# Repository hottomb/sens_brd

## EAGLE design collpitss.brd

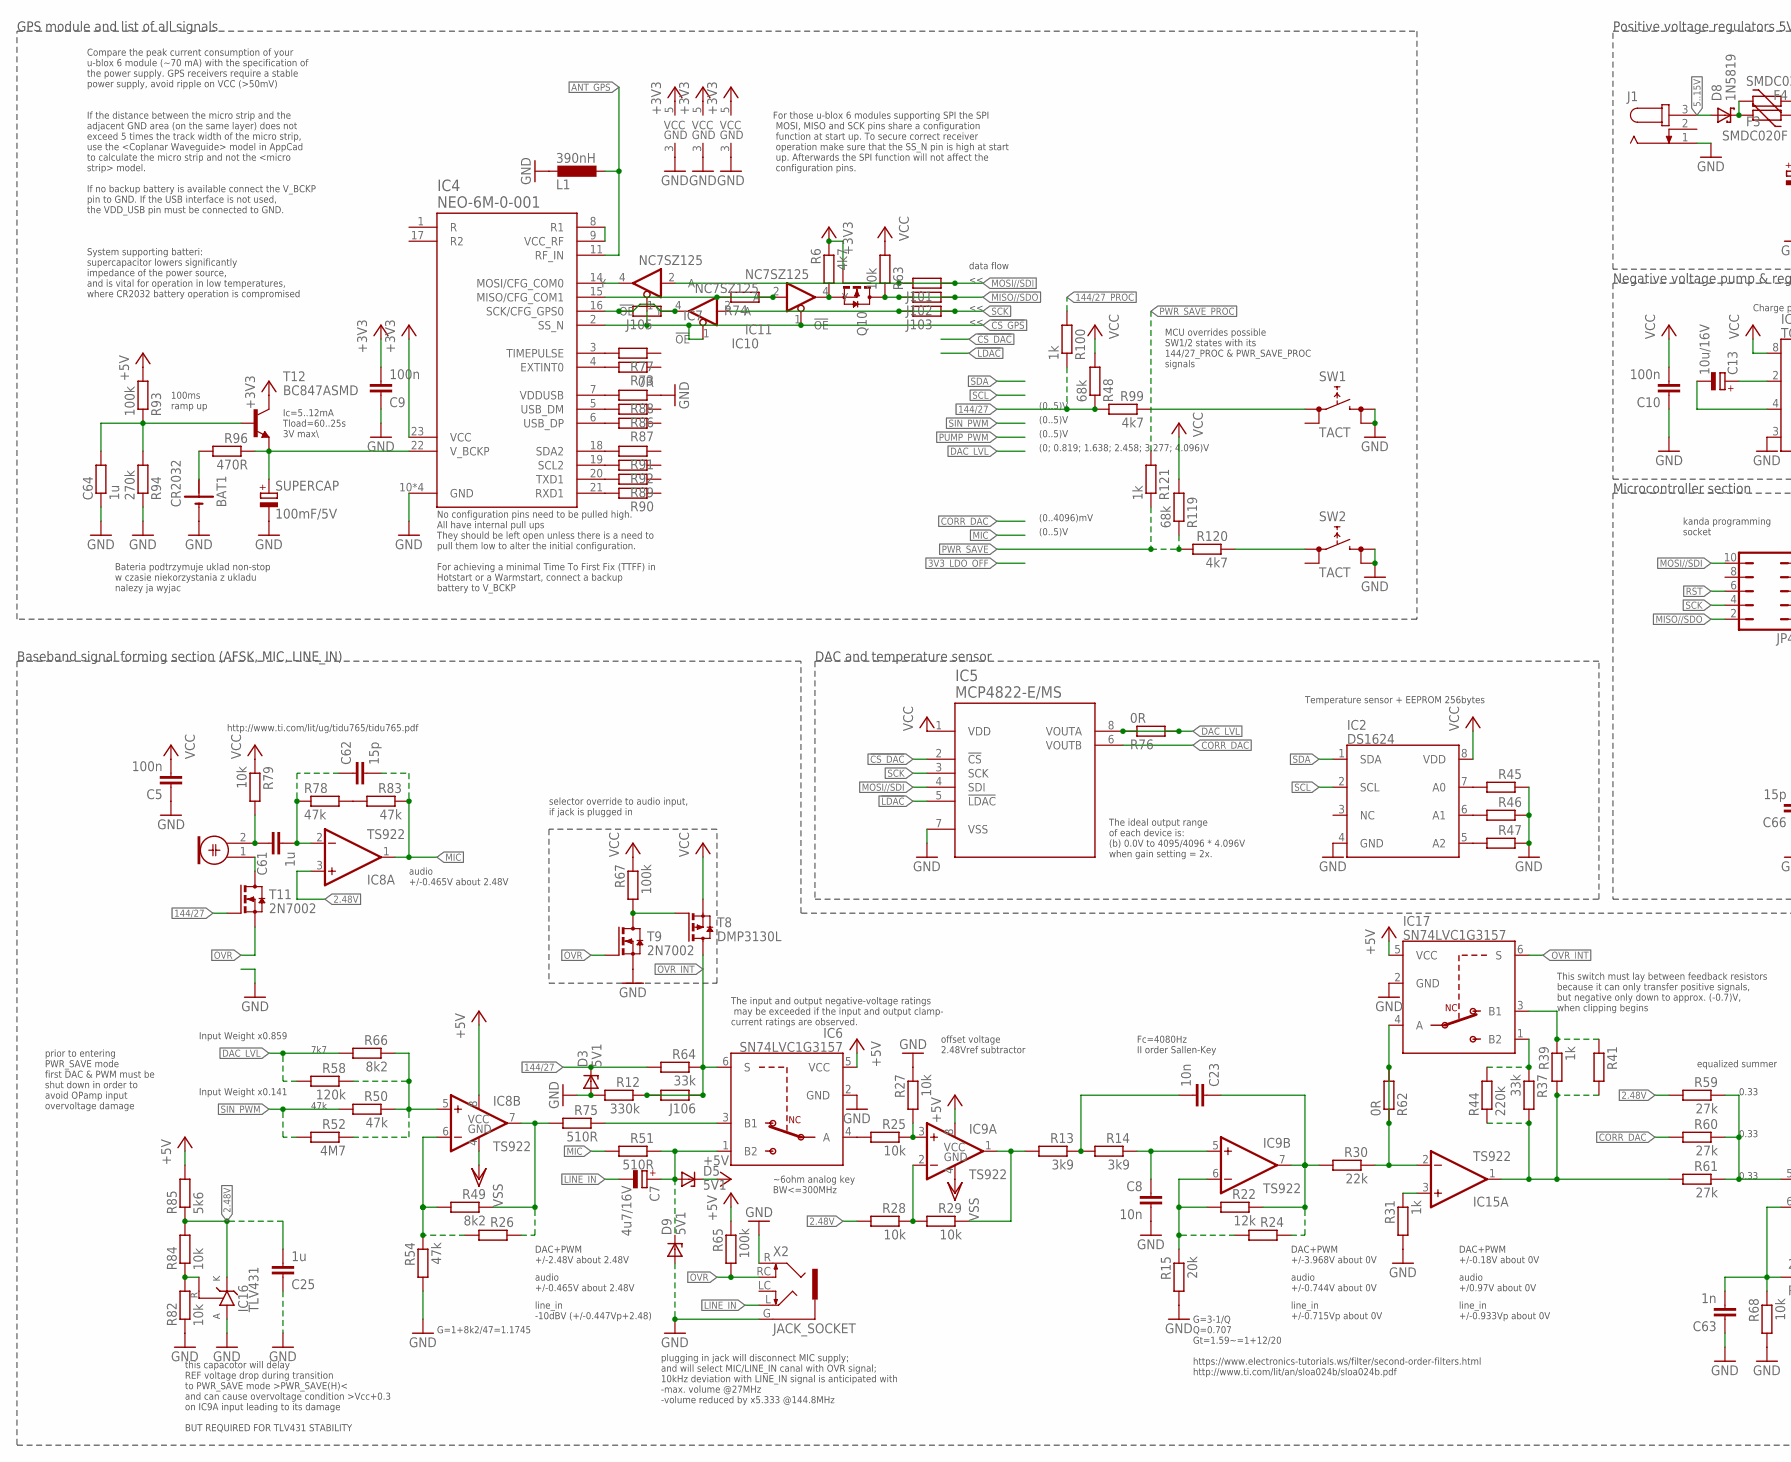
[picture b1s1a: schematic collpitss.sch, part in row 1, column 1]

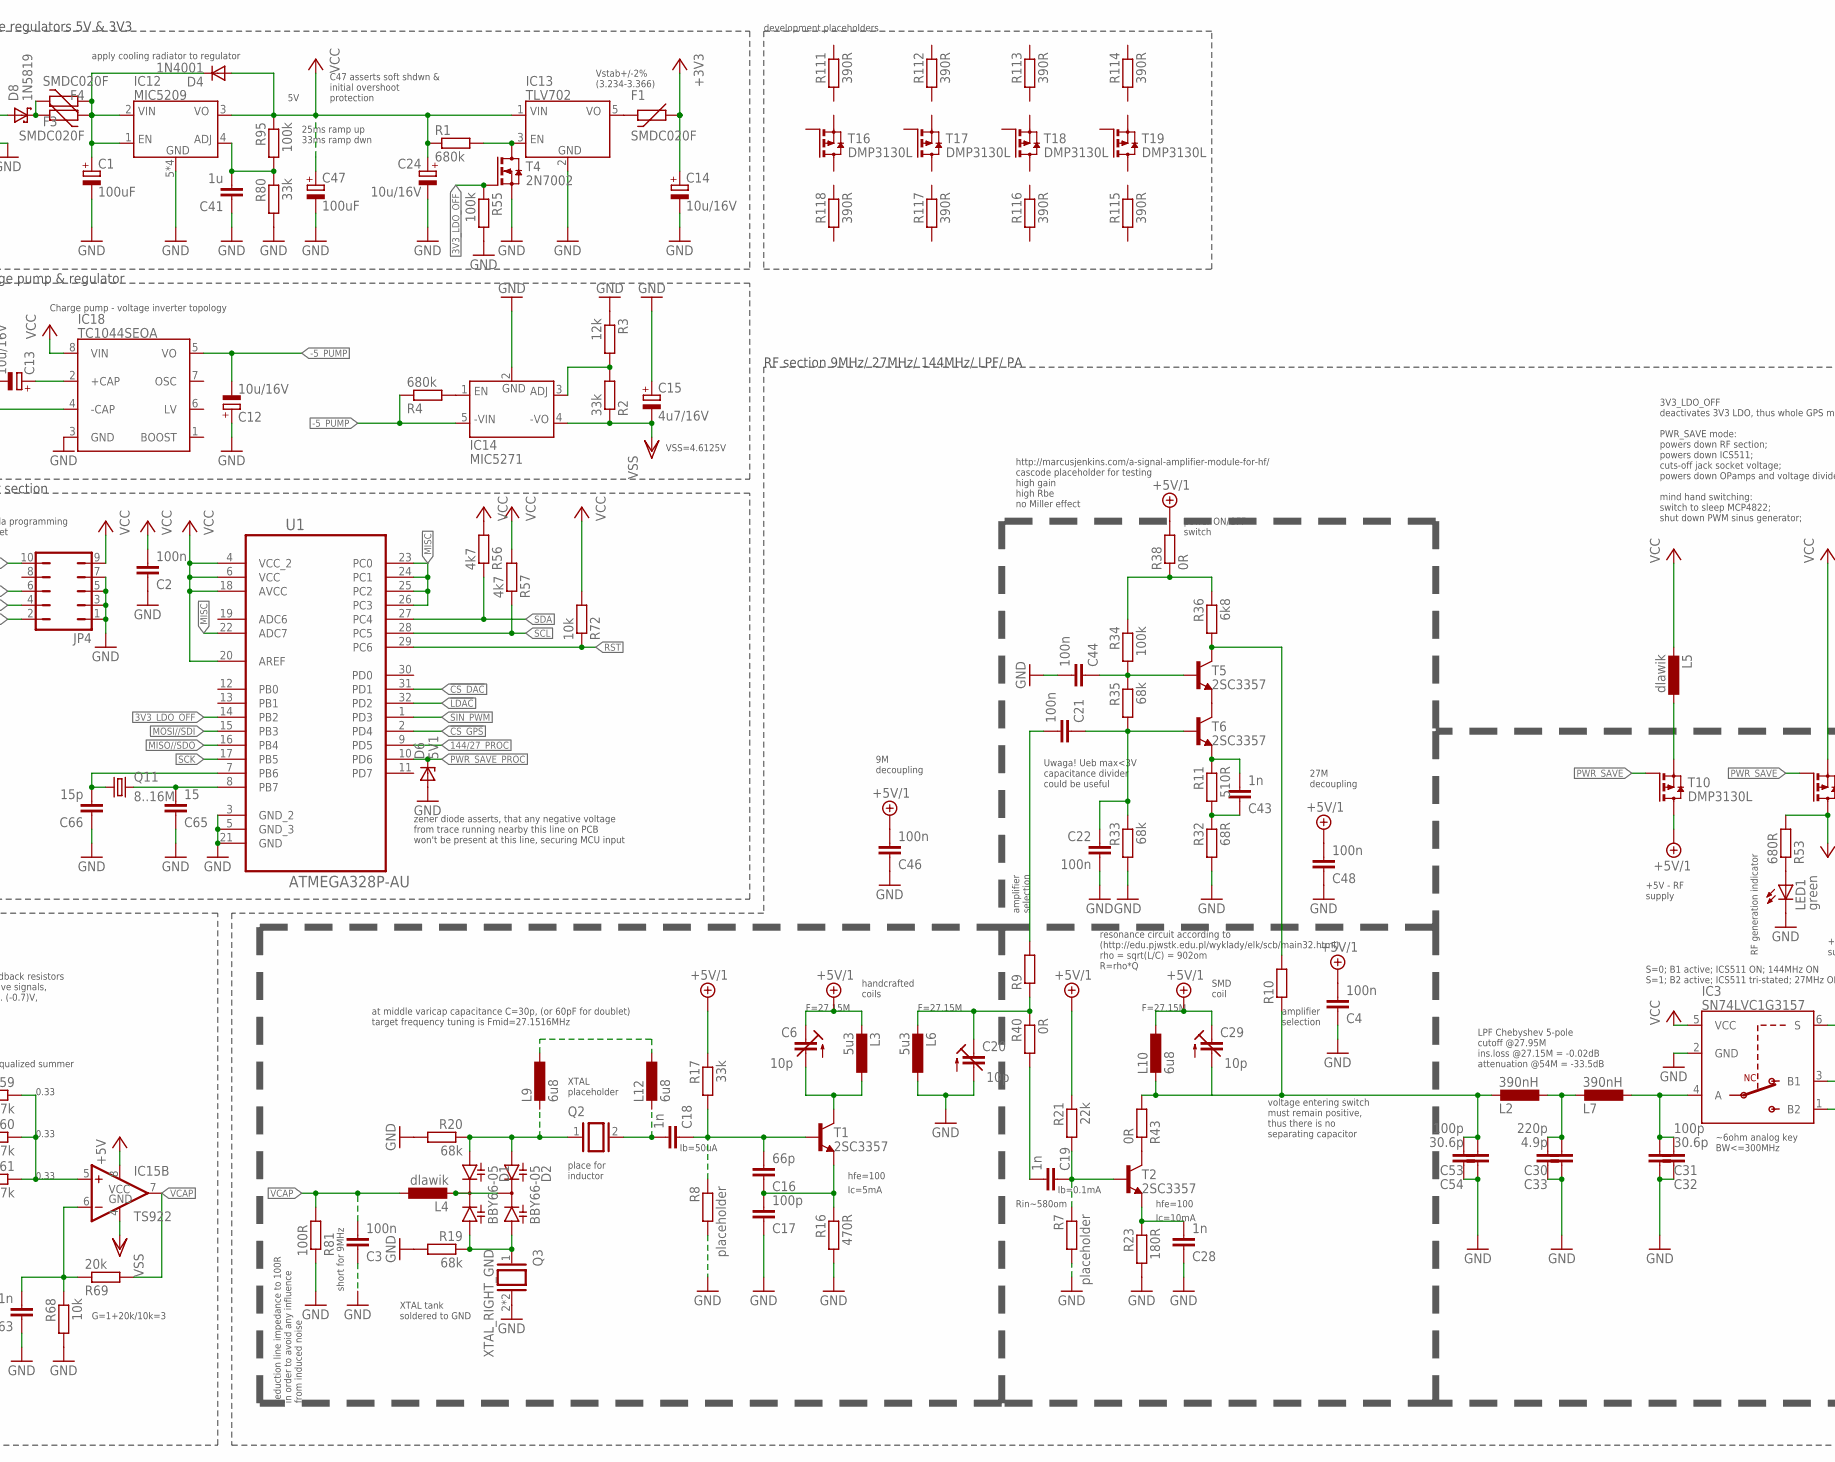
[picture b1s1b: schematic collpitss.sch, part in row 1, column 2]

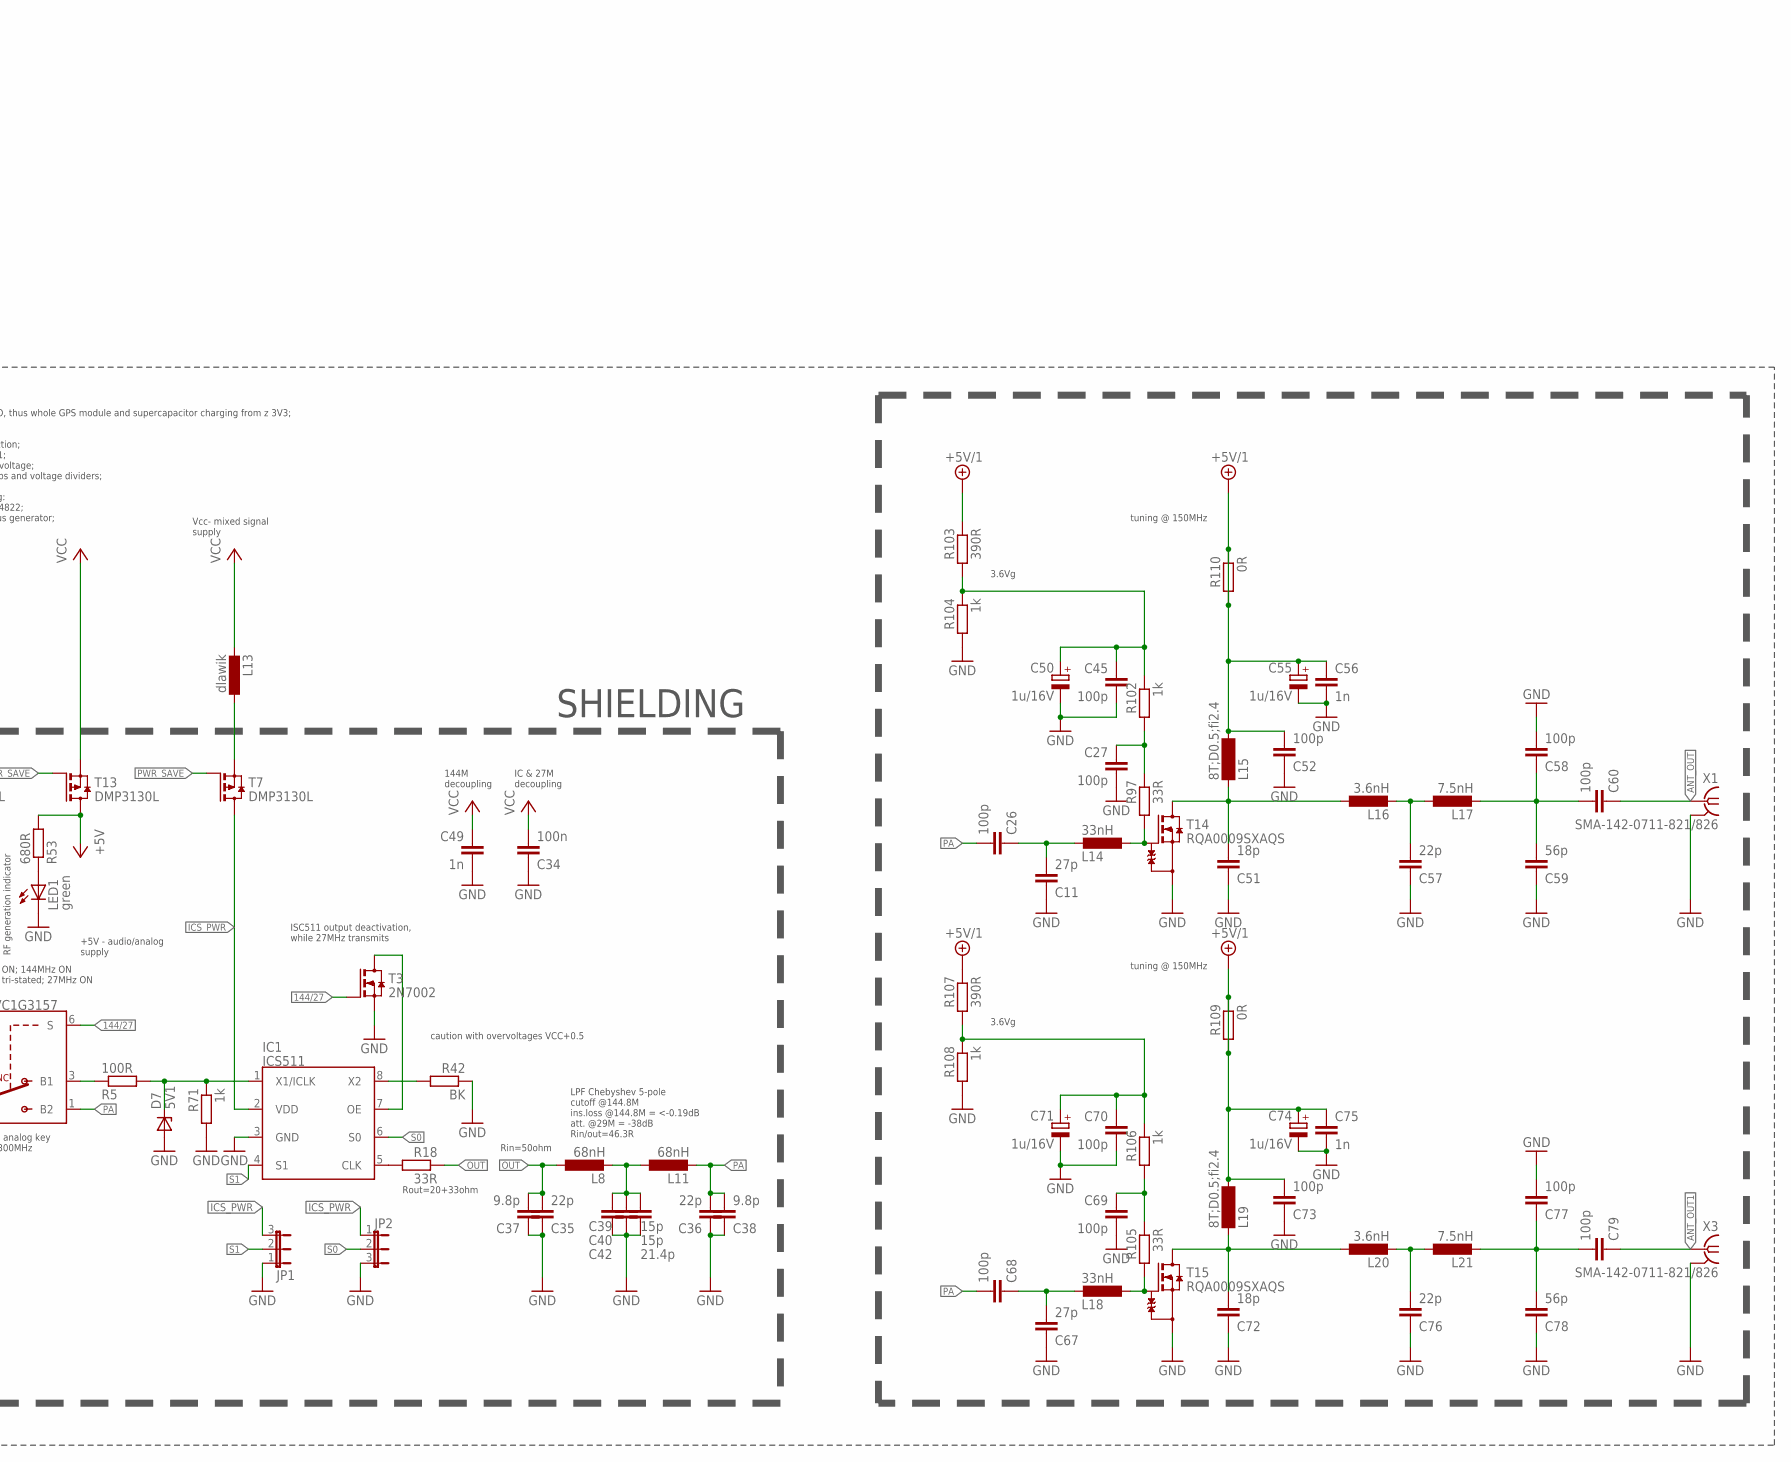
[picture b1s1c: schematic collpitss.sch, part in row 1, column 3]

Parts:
BAT1: CR2032; CR2032_HOLDER
C1, C47: 100uF; 153CLV-0605
C2, C3, C4, C5, C9, C10, C21, C22, C34, C44, C46, C48: 100n; C0805
C6, C20, C29: 10p; TZC3_SERIES
C7, C15: 4u7/16V; TANTAL"3216"
C8, C23: 10n; C0805
C11, C67: 27p; C0805
C12, C13, C14, C24: 10u/16V; TANTAL"3216"
C16: 66p; C0805
C17, C26, C27, C31, C45, C52, C53, C58, C60, C68, C69, C70, C73, C77, C79: 100p; C0805
C18, C19, C28, C43, C49, C56, C63, C75: 1n; C0603K
C25, C41: 1u; C1206
C30: 220p; C0805
C32, C54: 30.6p; C0805
C33: 4.9p; C0805
C35, C36, C57, C76: 22p; C0805
C37, C38: 9.8p; C0805
C39, C42, C62, C66: 15p; C0805
C40: 21.4p; C0805
C50, C55, C71, C74: 1u/16V; TANTAL"3216"
C51, C72: 18p; C0805
C59, C78: 56p; C0805
C61, C64: 1u; ZWORA
C65: 15; C0805
D1, D2: BBY66-05; SOT23-3
D3, D5, D6, D7, D9: 5V1; SOD323
D4: 1N4001; DO-214AC
D8: 1N5819; DO-214AC
F1, F3, F4: SMDC020F; 1812
IC1: ICS511; SOIC8
IC2: DS1624; SOIC8
IC3, IC6, IC17: SN74LVC1G3157; SC70-6
IC4: NEO-6M-0-001
IC5: MCP4822-E/MS; SOP65P490X110-8N
IC7, IC10, IC11: NC7SZ125; SC70-5
IC8, IC9, IC15: TS922; SO08
IC12: MIC5209; SOIC8
IC13: TLV702; SOT23-5
IC14: MIC5271; SOT23-5
IC16: TLV431; SOT23-3
IC18: TC1044SEOA; SOIC8
J1: JACK-PLUG1; SPC4078
J101, J102, J103, J105, J106: ZWORA
JP1, JP2: JP2E; JP2
JP4: JP5Q
L1, L2, L7: 390nH; 0603K
L3, L6: 5u3; L1812
L4, L5, L13: dlawik; 0806
L8, L11: 68nH; 0805
L9, L10, L12: 6u8; 1812
L14, L18: 33nH; 0603K
L15, L19: 8T;D0.5;fi2.4; SM-Z15
L16, L20: 3.6nH; 0805
L17, L21: 7.5nH; 0805
LED1: green; CHIP-LED0805
M1: ELECTRET_MICROPHON-WM-61A; WM-61A
Q2: XTAL"; Q"
Q3: XTAL_RIGHT_GND; Q
Q10: AO3402; SOT23-3
Q11: 8..16M; SM49
R1: 680k; ZWORA
R2, R17, R37, R64, R80: 33k; R0805
R3, R22: 12k; R0805
R4: 680k; R0805
R5, R81: 100R; R0805
R6, R56, R99, R120: 4k7; R0805
R7, R8: placeholder; R0805
R9, R10, R74: ZWORA
R11, R51, R75: 510R; R0805
R12: 330k; R0805
R13, R14: 3k9; R0805
R15, R69: 20k; R0805
R16: 470R; R0805
R18, R97, R105: 33R; R0805
R19, R20, R33, R35, R48, R119: 68k; R0805
R21, R30: 22k; R0805
R23: 180R; R0805
R24, R26, R41, R45, R46, R47, R73, R77, R86, R87, R89, R90, R91, R92: R-EU_R0805; R0805
R25, R27, R28, R29, R63, R68, R72, R79, R82, R84: 10k; R0805
R31, R39, R71, R100, R102, R104, R106, R108: 1k; R0805
R32: 68R; ZWORA
R34, R55, R67, R93, R95: 100k; R0805
R36: 6k8; R0805
R38, R40, R43: 0R; R1206
R42: BK; R0805
R44: 220k; R0805
R49, R66: 8k2; R0805
R50, R54, R78, R83: 47k; R0805
R52: 4M7; R0805
R53: 680R; ZWORA
R57: 4k7; ZWORA
R58: 120k; R0805
R59, R60, R61: 27k; R0805
R62, R76, R109, R110: 0R; ZWORA
R65: 100k; ZWORA
R85: 5k6; R0805
R88: 0R; R0805
R94: 270k; ZWORA
R96: 470R; ZWORA
R103, R107, R111, R112, R113, R114, R115, R116, R117, R118: 390R; R0805
R121: 1k; ZWORA
SUPERCAP: 100mF/5V; UD-10X10_NICHICON
SW1, SW2: TACT
T1, T2, T5, T6: 2SC3357; SOT-89-BCE
T3, T4, T9, T11: 2N7002; SOT23-3W
T7, T8, T10, T13, T16, T17, T18, T19: DMP3130L; SOT23-3
T12: BC847ASMD; SOT23
T14, T15: RQA0009SXAQS; SOT-89-GSD
U1: ATMEGA328P-AU; QFP80P900X900X120-32N
X1, X3: SMA-142-0711-821/826; J502-ND-142-0711-821/826
X2: JACK_SOCKET

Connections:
2.48V: C25.2, IC8.3 (+IN), IC16.2 (K), R28.2, R59.2, R84.2, R85.1
3V3_LDO_OFF: R55.1, T4.1 (G), U1.14 (PB2)
5..15V: D8.A, J1.3
144/27: D3.C (K), IC3.6 (S), R48.1, R64.2, R99.2, R100.1, T3.1 (G), T11.1 (G)
144/27_PROC: R100.2, U1.9 (PD5)
!CS_DAC!: IC5.2 (!CS!), U1.31 (PD1)
!CS_GPS!: IC4.2 (SS_N), IC7.1 (!OE!), IC10.1 (!OE!), IC11.1 (!OE!), U1.2 (PD4)
!LDAC!: IC5.5 (!LDAC!), U1.32 (PD2)
+3V3: C9.2, C14.+, F1.P$2 (2), IC4.23 (VCC), IC7.5 (VCC), IC10.5 (VCC), IC11.5 (VCC), Q10.1 (G), R6.1, T12.3 (C)
+5V: D5.C (K), IC6.5 (VCC), IC8.8 (VCC), IC9.8 (VCC), IC15.8 (VCC), IC17.5 (VCC), R53.2, R65.1, R85.2, R93.2, T13.3 (D)
+5V/1: C4.2, C6.2 (E), C29.2 (E), C46.2, C48.2, C52.2, C55.+, C56.1, C73.2, C74.+, C75.1, L3.2, L10.1, L15.2, L19.2, R17.1, R21.1, R38.2, R103.1, R107.1, R109.1, R109.2, R110.1, R110.2, T10.3 (D)
-5_PUMP: C12.-, IC14.5 (-VIN), IC18.5 (VO), R4.1
ANT_GPS: IC4.11 (RF_IN), L1.1
ANT_OUT: C60.1, X1.1
ANT_OUT1: C79.1, X3.1
ASASA: D8.C (K), F3.P$1 (1), F4.P$2 (2)
CAS_IN: C20.2 (E), L6.2, R9.1, R40.1
CORR_DAC: IC5.6 (VOUTB), R60.2
DAC_LVL: IC5.8 (VOUTA), R58.2, R66.2, R76.1, R76.2
GND: BAT1.-, C1.-, C2.1, C3.1, C4.1, C5.1, C8.2, C9.1, C10.1, C11.1, C12.+, C14.-, C15.+, C17.1, C20.1 (A), C22.2, C24.-, C25.1, C27.2, C28.1, C30.1, C31.1, C32.1, C33.1, C34.1, C35.1, C36.1, C37.1, C38.1, C39.1, C40.1, C41.1, C42.1, C44.2, C45.2, C46.1, C47.-, C48.1, C49.2, C50.-, C51.1, C52.1, C53.1, C54.1, C55.-, C56.2, C57.1, C58.2, C59.1, C63.1, C64.1, C65.1, C66.1, C67.1, C69.2, C70.2, C71.-, C72.1, C73.1, C74.-, C75.2, C76.1, C77.2, C78.1, D3.A, D6.A, D7.A, D9.A, IC1.3 (GND), IC2.4 (GND), IC3.2 (GND), IC4.10 (GND), IC4.12 (GND), IC4.13 (GND), IC4.24 (GND), IC5.7 (VSS), IC6.2 (GND), IC7.3 (GND), IC10.3 (GND), IC11.3 (GND), IC12.5 (GND), IC12.6 (GND), IC12.7 (GND), IC12.8 (GND), IC13.2 (GND), IC14.2 (GND), IC16.3 (A), IC17.2 (GND), IC18.3 (GND), J1.1, JP1.1, JP2.3, JP4.1, JP4.3, JP4.5, JP4.7, L1.2, L6.1, LED1.C, Q3.2, Q3.P$1 (2), R3.1, R7.2, R8.2, R12.2, R15.2, R16.2, R19.2, R20.2, R23.2, R27.1, R31.2, R32.2, R33.2, R42.1, R45.1, R46.1, R47.1, R54.2, R55.2, R68.2, R71.2, R80.2, R81.1, R82.1, R88.1, R94.1, R104.2, R108.2, SUPERCAP.-, SW1.2, SW1.3, SW2.2, SW2.3, T3.2 (S), T4.2 (S), T9.2 (S), T14.2 (S), T14.2@1 (S), T15.2 (S), T15.2@1 (S), U1.3 (GND_2), U1.5 (GND_3), U1.21 (GND), X1.G@1 (2), X1.G@2 (2), X1.G@3 (2), X1.G@4 (2), X2.G (GND), X2.R, X3.G@1 (2), X3.G@2 (2), X3.G@3 (2), X3.G@4 (2)
ICS_PWR: IC1.2 (VDD), JP1.3, JP2.1, T7.3 (D)
J104: IC4.15 (MISO/CFG_COM1), IC11.2 (A), R74.1, R74.2
LINE_IN: C7.-, X2.L
LOLOLO: IC13.3 (EN), R1.2, T4.3 (D)
MIC: C62.2, IC8.1 (OUT), R51.2, R83.1
MISC: U1.22 (ADC7), U1.23 (PC0), U1.24 (PC1), U1.25 (PC2), U1.26 (PC3)
MISO//SDO: J102.1, J102.2, JP4.2, Q10.3 (D), R63.1, U1.16 (PB4)
MOSI//SDI: IC5.4 (SDI), IC7.2 (A), J101.1, J101.2, JP4.10, U1.15 (PB3)
unnamed: C31.2, C32.2, IC3.4 (A), L7.1
unnamed: D1.3 (K), D2.3 (K), L4.2
unnamed: C1.+, D4.C (K), F3.P$2 (2), F4.P$1 (1), IC12.1 (EN), IC12.2 (VIN)
unnamed: F1.P$1 (1), IC13.5 (VO)
unnamed: BAT1.+, R96.2
unnamed: IC14.3 (ADJ), R2.2, R3.2
unnamed: C6.1 (A), L3.1, T1.C, T1.C@1 (C)
unnamed: IC3.3 (B1), R5.1
unnamed: L5.1, T10.2 (S)
unnamed: IC1.7 (OE), T3.3 (D)
unnamed: IC14.1 (EN), R4.2
unnamed: C23.2, R13.1, R14.2
unnamed: D1.2 (A2), D2.2 (A2), Q3.1, R19.1
unnamed: IC11.4 (Y), Q10.2 (S), R6.2
unnamed: D1.1 (A1), D2.1 (A1), L9.2, Q2.1, R20.1
unnamed: C18.2, L12.2, Q2.2
unnamed: L9.1, L12.1
unnamed: C16.2, C18.1, R8.1, R17.2, T1.B
unnamed: C29.1 (A), C53.2, C54.2, L2.2, L10.2, R10.1, R43.2
unnamed: C23.1, IC9.7 (OUT), R22.1, R24.1, R30.2
unnamed: C8.1, IC9.5 (+IN), R14.1
unnamed: IC9.6 (-IN), R15.1, R22.2, R24.2
unnamed: C28.2, R23.1, T2.E
unnamed: IC6.4 (A), R25.2
unnamed: C19.1, R7.1, R21.2, T2.B
unnamed: IC9.3 (+IN), R25.1, R27.2
unnamed: IC9.2 (-IN), R28.1, R29.2
unnamed: IC15.3 (+IN), R31.1
unnamed: IC9.1 (OUT), R13.2, R29.1
unnamed: IC17.3 (B1), R39.1, R41.1
unnamed: IC15.1 (OUT), R37.2, R39.2, R41.2, R44.1, R61.2
unnamed: C16.1, C17.2, R16.1, T1.E
unnamed: IC17.1 (B2), R37.1, R44.2
unnamed: R99.1, SW1.1
unnamed: L13.1, T7.2 (S)
unnamed: IC15.2 (-IN), IC17.4 (A), R30.1, R62.1, R62.2
unnamed: C13.+, IC18.2 (+CAP)
unnamed: C11.2, C26.1, L14.2
unnamed: C13.-, IC18.4 (-CAP)
unnamed: C27.1, R97.1, R102.2
unnamed: C21.2, R9.2
unnamed: C67.2, C68.1, L18.2
unnamed: L18.1, R105.2, T15.1 (G)
unnamed: L14.1, R97.2, T14.1 (G)
unnamed: C51.2, L15.1, L16.1, T14.3 (D)
unnamed: C57.2, L16.2, L17.1
unnamed: C69.1, R105.1, R106.2
unnamed: T5.E, T6.C, T6.C@1 (C)
unnamed: C43.2, R11.1, T6.E
unnamed: C43.1, R11.2, R32.1
unnamed: C44.1, R34.2, R35.1, T5.B
unnamed: C39.2, C40.2, C42.2, L8.2, L11.1
unnamed: C58.1, C59.2, C60.2, L17.2
unnamed: C19.2, R40.2
unnamed: C21.1, C22.1, R33.1, R35.2, T6.B
unnamed: R10.2, R36.2, T5.C, T5.C@1 (C)
unnamed: R34.1, R36.1, R38.1
unnamed: IC1.5 (CLK), R18.2
unnamed: R43.1, T2.C, T2.C@1 (C)
unnamed: IC1.8 (X2), R42.2
unnamed: C72.2, L19.1, L20.1, T15.3 (D)
unnamed: C41.2, IC12.4 (ADJ), R80.1, R95.2
unnamed: R67.2, T8.1 (G), T9.3 (D)
unnamed: C45.1, C50.+, R102.1, R103.2, R104.1
unnamed: IC2.7 (A0), R45.2
unnamed: IC2.6 (A1), R46.2
unnamed: IC2.5 (A2), R47.2
unnamed: C76.2, L20.2, L21.1
unnamed: IC8.7 (OUT), R26.1, R49.1, R75.2
unnamed: C7.+, D5.A, D9.C (K), IC6.1 (B2), R51.1
unnamed: D7.C (K), IC1.1 (X1/ICLK), R5.2, R71.1
unnamed: C77.1, C78.2, C79.2, L21.2
unnamed: C30.2, C33.2, L2.1, L7.2
unnamed: C70.1, C71.+, R106.1, R107.2, R108.1
unnamed: IC8.5 (+IN), R50.1, R52.1, R58.1, R66.1
unnamed: R120.1, SW2.1
unnamed: IC4.22 (V_BCKP), R96.1, SUPERCAP.+, T12.2 (E)
unnamed: IC4.4 (EXTINT0), R73.2
unnamed: C63.2, IC15.6 (-IN), R68.1, R69.1
unnamed: IC15.5 (+IN), R59.1, R60.1, R61.1
unnamed: IC4.3 (TIMEPULSE), R77.2
unnamed: C61.1, M1.2, R79.2
unnamed: IC6.3 (B1), R75.1
unnamed: R78.2, R83.2
unnamed: IC4.14 (MOSI/CFG_COM0), IC7.4 (Y)
unnamed: IC4.16 (SCK/CFG_GPS0), IC10.4 (Y), J105.1, J105.2
unnamed: C61.2, C62.1, IC8.2 (-IN), R78.1
unnamed: LED1.A, R53.1
unnamed: IC8.6 (-IN), R26.2, R49.2, R54.1
unnamed: IC16.1 (R), R82.2, R84.1
unnamed: IC4.5 (USB_DM), R86.2
unnamed: IC4.6 (USB_DP), R87.2
unnamed: IC4.7 (VDDUSB), R88.2
unnamed: IC4.20 (TXD1), R89.2
unnamed: IC4.21 (RXD1), R90.2
unnamed: IC4.18 (SDA2), R91.2
unnamed: IC4.19 (SCL2), R92.2
unnamed: IC4.8 (R1), IC4.9 (VCC_RF)
unnamed: C65.2, Q11.2, U1.8 (PB7)
unnamed: C64.2, R93.1, R94.2, T12.1 (B)
unnamed: C66.2, Q11.1, U1.7 (PB6)
unnamed: M1.1, T11.3 (D)
OUT: C35.2, C37.2, L8.1, R18.1
OVR: R65.2, T9.1 (G), T11.2 (S), X2.RC
OVR_INT: IC6.6 (S), IC17.6 (S), J106.1, J106.2, R12.1, R64.1, T8.3 (D)
PA: C26.2, C36.2, C38.2, C68.2, IC3.1 (B2), L11.2
PWR_SAVE: R119.1, R120.2, R121.1, T7.1 (G), T10.1 (G), T13.1 (G)
PWR_SAVE_PROC: D6.C (K), R121.2, U1.10 (PD6)
RST: JP4.6, R72.1, U1.29 (PC6)
S0: IC1.6 (S0), JP2.2
S1: IC1.4 (S1), JP1.2
SCK: IC5.3 (SCK), IC10.2 (A), J103.1, J103.2, JP4.4, U1.17 (PB5)
SCL: IC2.2 (SCL), R57.1, U1.28 (PC5)
SDA: IC2.1 (SDA), R56.1, U1.27 (PC4)
SIN_PWM: R50.2, R52.2, U1.1 (PD3)
VCAP: C3.2, IC15.7 (OUT), L4.1, R69.2, R81.2
VCC: C2.2, C5.2, C10.2, C24.+, C34.2, C47.+, C49.1, D4.A, IC2.8 (VDD), IC3.5 (VCC), IC5.1 (VDD), IC12.3 (VO), IC13.1 (VIN), IC18.8 (VIN), JP4.9, L5.2, L13.2, R1.1, R48.2, R56.2, R57.2, R63.2, R67.1, R72.2, R79.1, R95.1, R119.2, T8.2 (S), T13.2 (S), U1.4 (VCC_2), U1.6 (VCC), U1.18 (AVCC), U1.20 (AREF)
VSS: C15.-, IC8.4 (GND), IC9.4 (GND), IC14.4 (-VO), IC15.4 (GND), R2.1

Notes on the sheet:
at middle varicap capacitance C=30p, (or 60pF for doublet) target frequency tuning is Fmid=27.1516MHz
XTAL tank soldered to GND
hfe=100
F=27.15M
handcrafted coils
Ic=10mA
Ib=0.1mA
Ib=50uA
SMD coil
Ic=5mA
resonance circuit according to (http://edu.pjwstk.edu.pl/wyklady/elk/scb/main32.html) rho = sqrt(L/C) = 902om R=rho*Q
Rin~580om
XTAL placeholder
LPF Chebyshev 5-pole cutoff @27.95M ins.loss @27.15M = -0.02dB attenuation @54M = -33.5dB
LPF Chebyshev 5-pole cutoff @144.8M ins.loss @144.8M = <-0.19dB att. @29M = -38dB Rin/out=46.3R
144M decoupling
IC & 27M decoupling
http://marcusjenkins.com/a-signal-amplifier-module-for-hf/ cascode placeholder for testing high gain high Rbe no Miller effect
amplifier selection
power ON/OFF switch
9M decoupling
27M decoupling
~6ohm analog key BW<=300MHz
Rin=50ohm
Rout=20+33ohm
S=0; B1 active; ICS511 ON; 144MHz ON S=1; B2 active; ICS511 tri-stated; 27MHz ON
47k
7k7
G=1+8k2/47=1.1745
(0..5)V
(0; 0.819; 1.638; 2.458; 3.277; 4.096)V
G=1+20k/10k=3
(0..4096)mV
0.33
Temperature sensor + EEPROM 256bytes
Charge pump - voltage inverter topology
equalized summer
http://www.ti.com/lit/ug/tidu765/tidu765.pdf
The ideal output range of each device is: (b) 0.0V to 4095/4096 * 4.096V when gain setting = 2x.
audio +/-0.465V about 2.48V

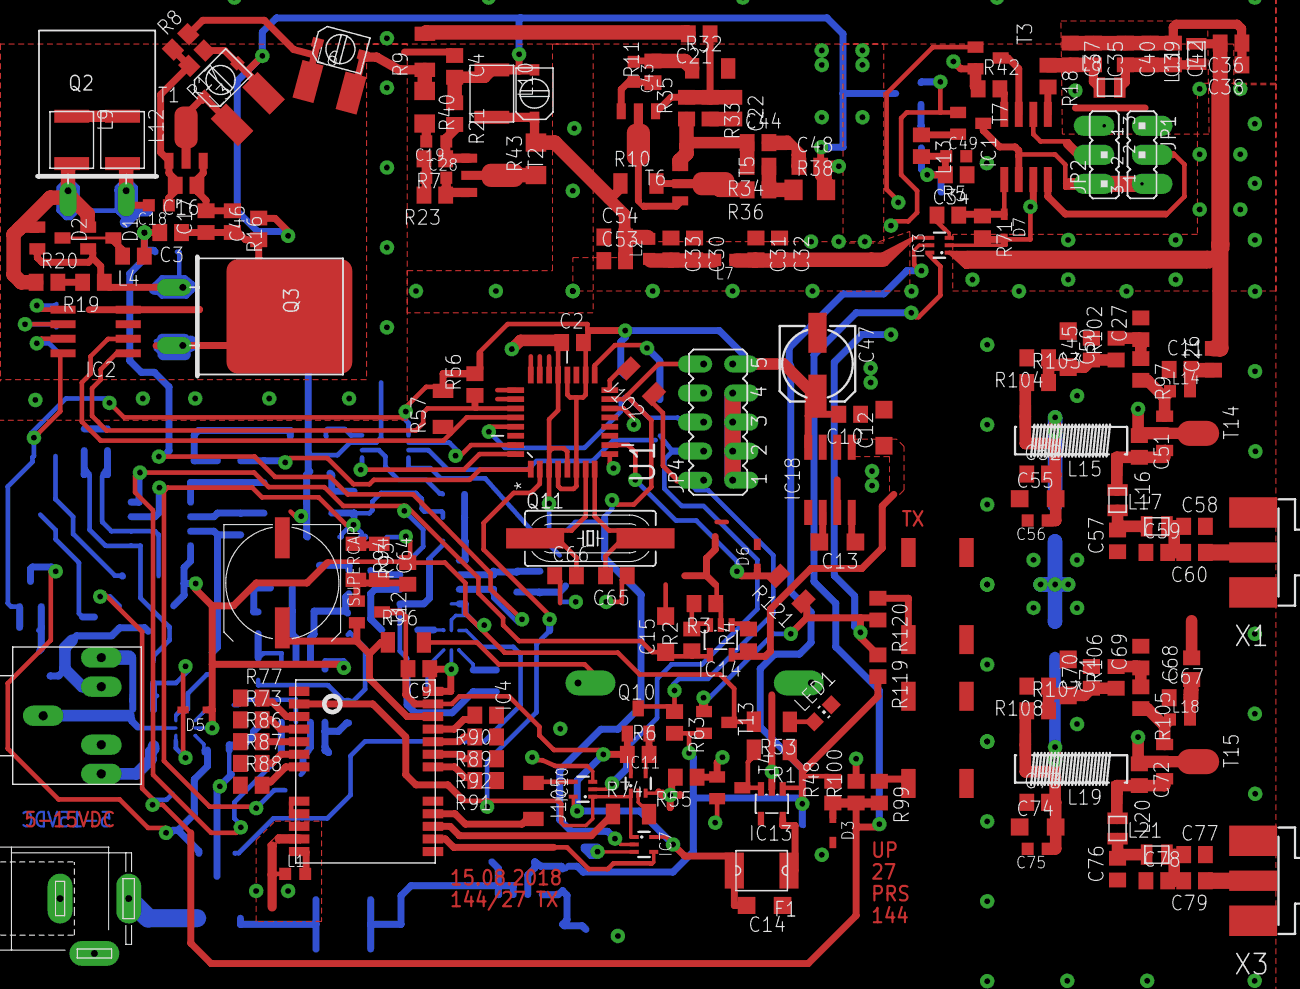
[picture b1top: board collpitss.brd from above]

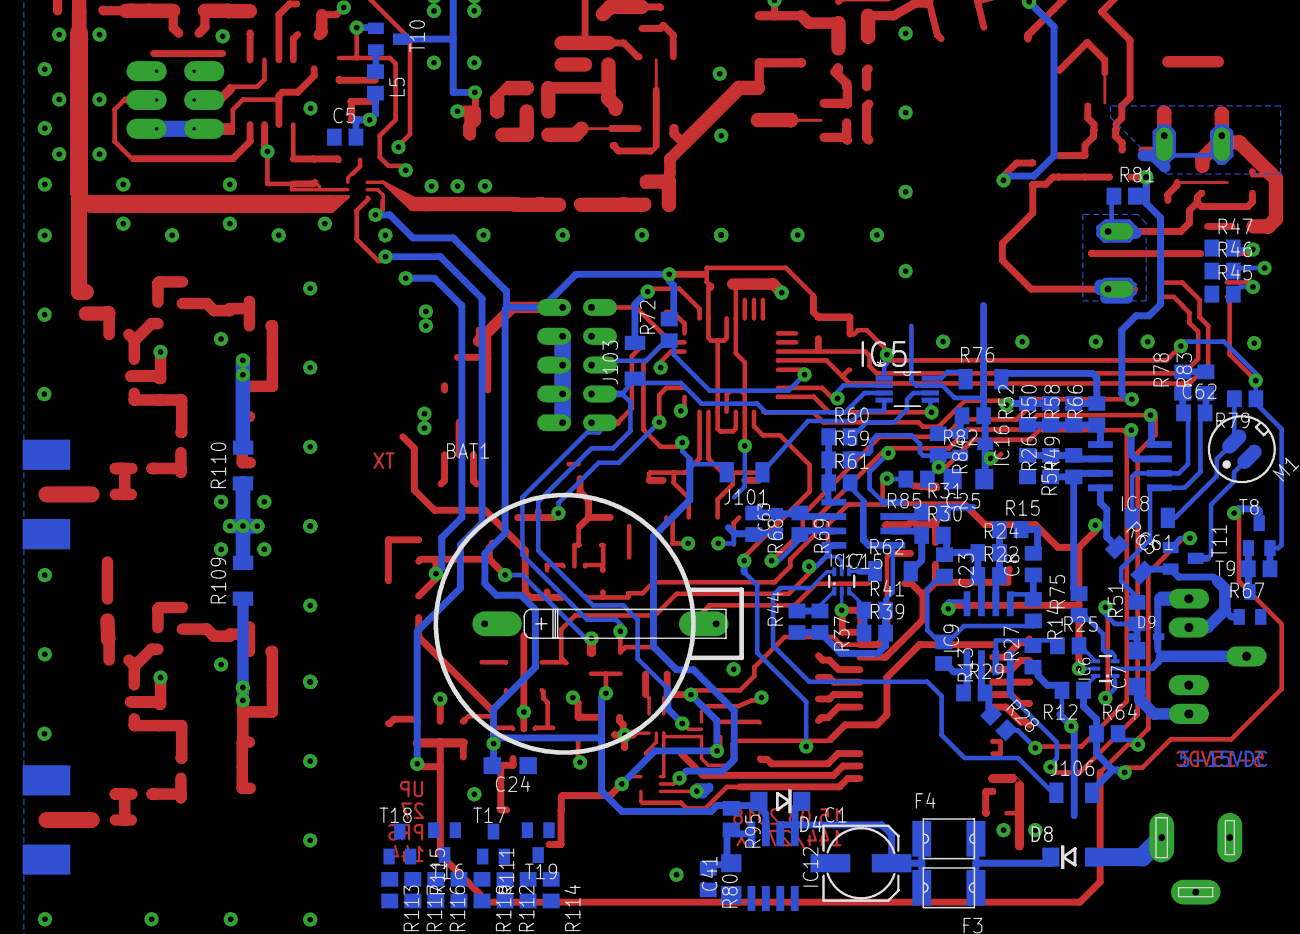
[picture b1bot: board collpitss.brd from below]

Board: 2 copper layers, 290 parts (96 on the bottom side), 146 nets.
